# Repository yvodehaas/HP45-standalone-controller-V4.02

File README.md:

# HP45-standalone-controller-V4.02
HP45 standalone controller V4.02

This github repository is a direct upload of the HP45 Standalone controller V4.02.

This version uses a Teensy 3.5, has all the extra circuits to use DMA for inkjet, and has self testing capabilities. 
A more detailed set of information can be found here: https://ytec3d.com/hp45-controller-v4/

The firmware to run on this board is found here: https://github.com/yvodehaas/HP45-standalone-V4
And the software to control it is found here: https://github.com/yvodehaas/Inkjet-commander
Oasis controller also works on this controller, though it will only work in an Oasis based machine: https://hackaday.io/project/86954-oasis-3dp

This project has been discontinued on my side and is uploaded in the hope that someone else can use it as a template or as is. It is provided without warranty.

The board has a few known issues to keep in mind:
- The reset pulse circuit that resets the TLC59213 using the 74HC123 NEEDS to work. Without this the TLC59213 stays powered. Best case this destroys the HP45 nozzles on the HP45, works case it first destroys the TLC59213, then the Teensy 3.5
- The TLC59213 has a direct connection to the Teensy 3.5. The TLC59213 breaking usually applies the 12V supply to the Teensy 3.5 pins, destroying it.
- The Address testing circuit sometimes gives false negatives. The controller will still print, but while throwing errors.
- The resistor accross the 4017 and 4081 circuit (address circuit) is there to raise the voltage for the nozzle check circuit. The HP45 has pulldown resistors that lowered the voltage on the test circuit sufficiently to stop being able to test.
- Temperature is an indication. The formula was based on 2 printheads while it is known that the HP45 has no accurate temperature sensor. 80C at startup is possible.
- The controller needs 3 pulses to fire all nozzles in an address. This is done 5 primitives, 5 primitives and 4 primitives on each address. This seems to be an issue in the HP45, where too much heat builds up, leading to misfirings. Varying the voltage on the VHD should make this better, but this needs to be calibrated for each printhead.

This list will get appended when more issues are found.

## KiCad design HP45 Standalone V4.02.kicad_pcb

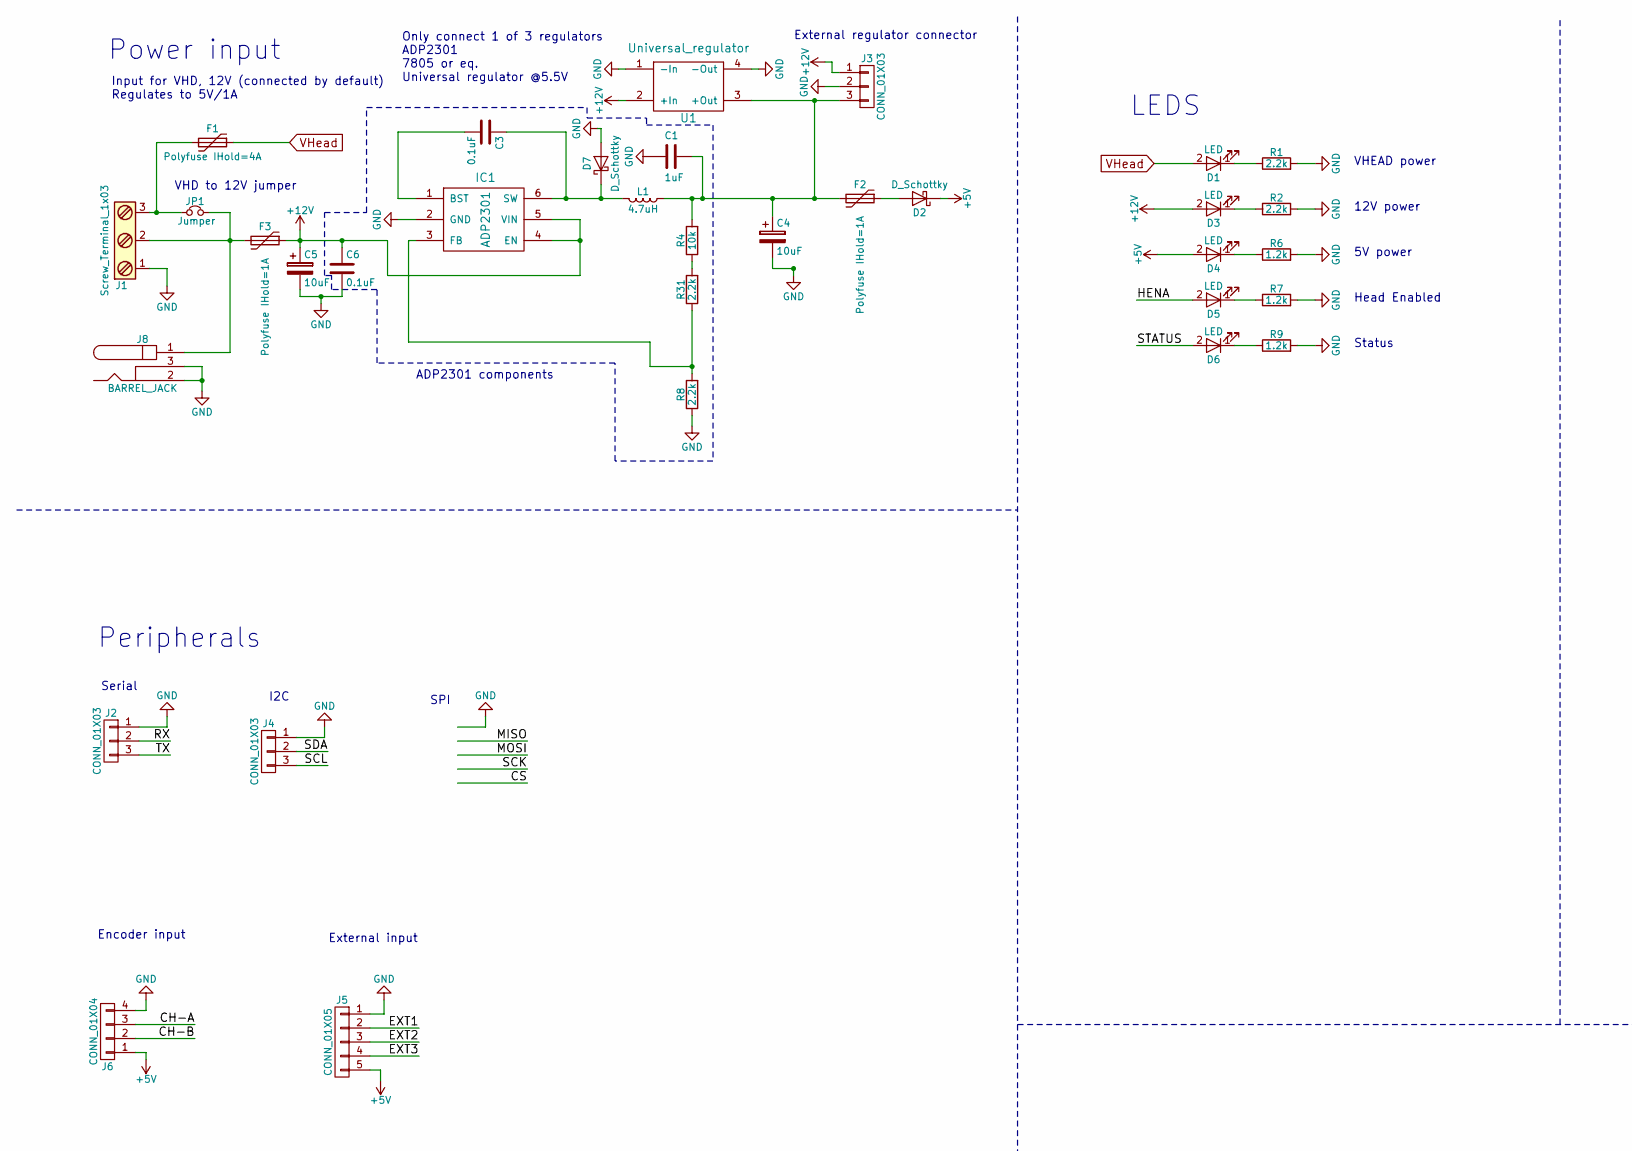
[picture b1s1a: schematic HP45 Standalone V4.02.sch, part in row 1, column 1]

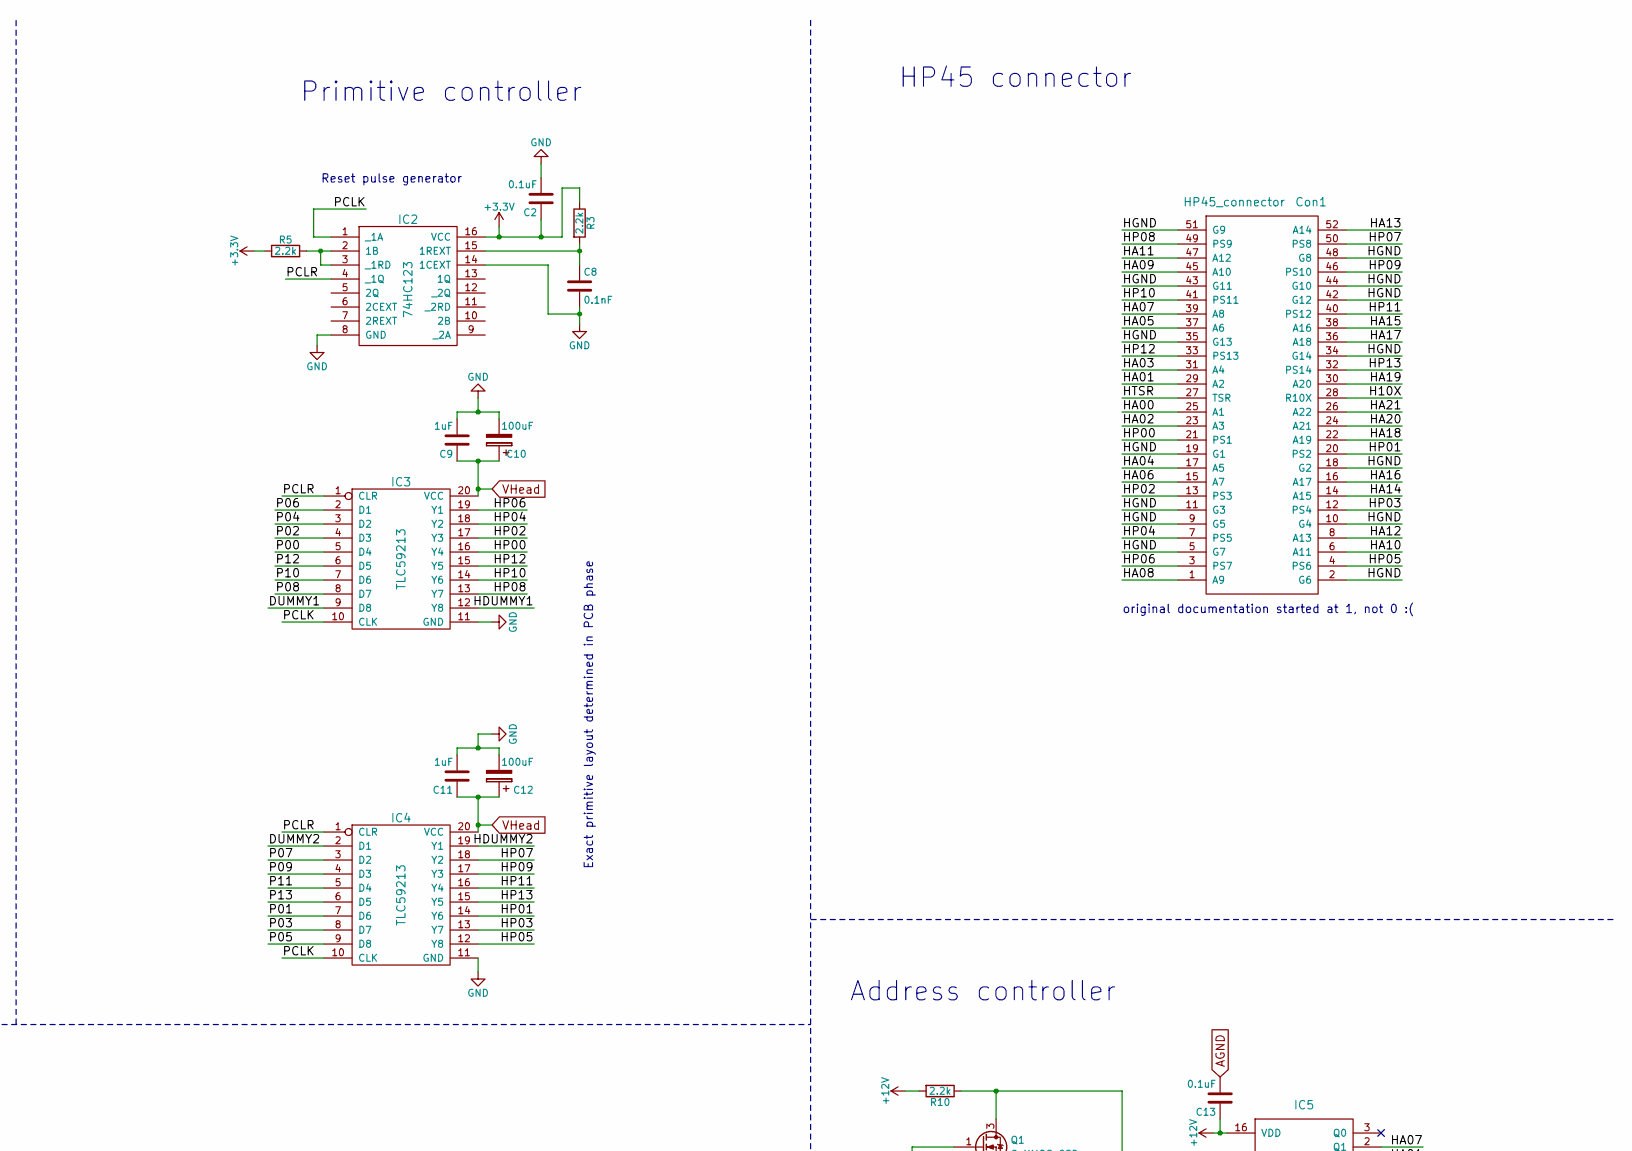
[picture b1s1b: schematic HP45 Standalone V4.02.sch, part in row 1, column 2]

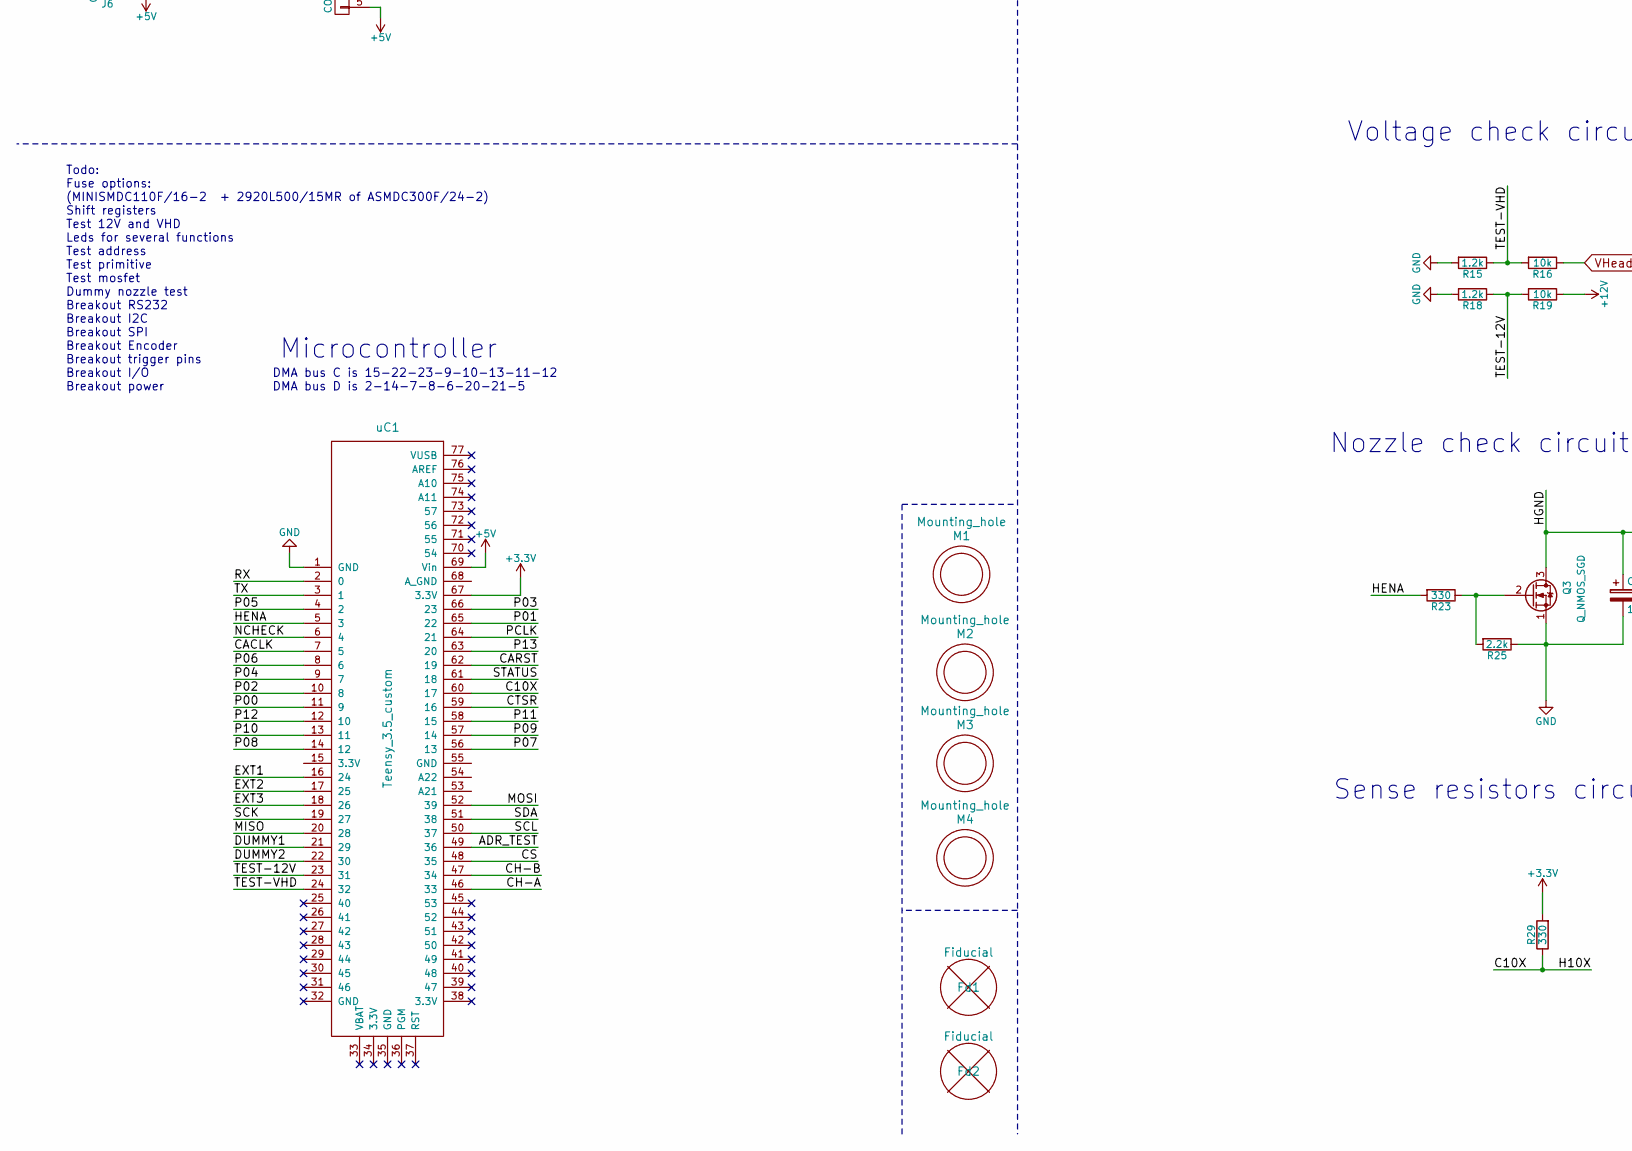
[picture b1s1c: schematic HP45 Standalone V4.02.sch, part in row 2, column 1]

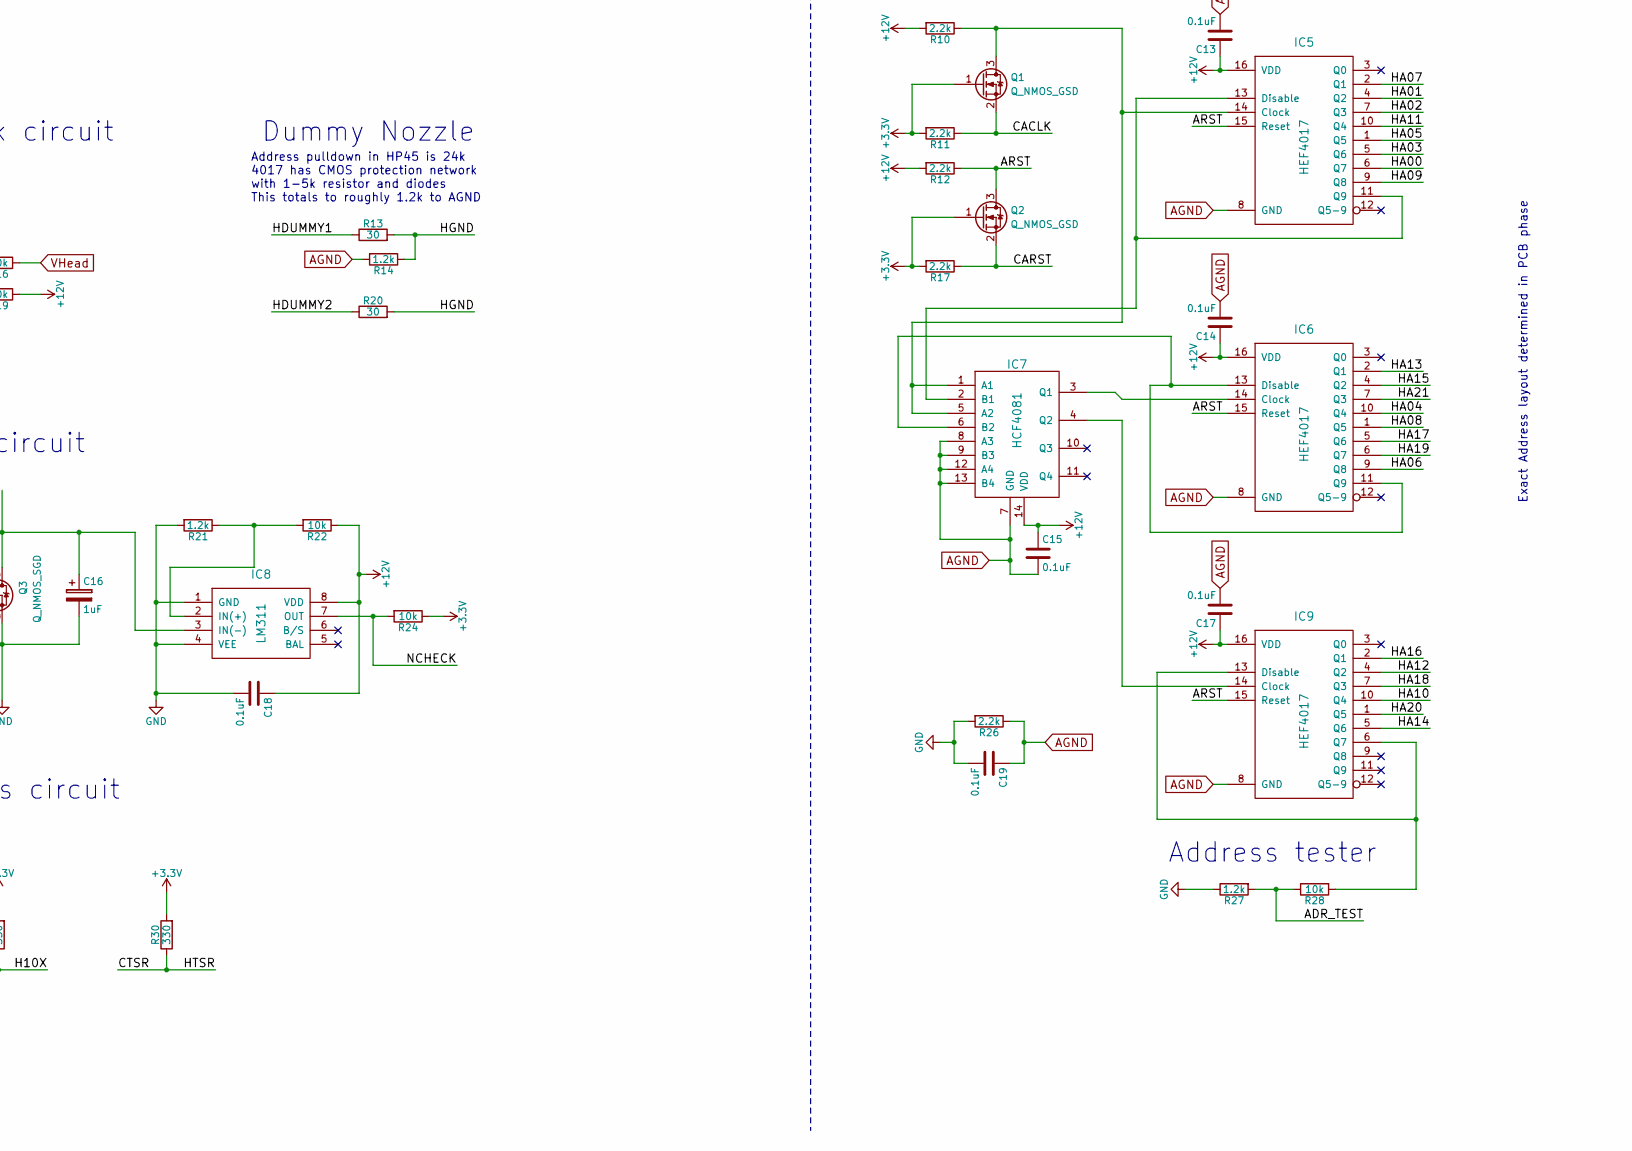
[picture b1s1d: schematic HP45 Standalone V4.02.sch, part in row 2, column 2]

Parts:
C1, C9, C11: 1uF; C_0603
C2, C3, C6, C13, C14, C15, C17, C18, C19: 0.1uF; C_0603
C4, C5: 10uF; CP_Elec_4x5.8
C8: 0.1nF; C_0603
C10, C12: 100uF; CP_Elec_8x10
C16: 1uF; CP_Elec_4x5.8
Con1: HP45_connector; HP45_SMD_connector
D1, D3, D4, D5, D6: LED; LED_0603
D2, D7: D_Schottky; D_SOD-323HE
F1: Polyfuse IHold=4A; Universal_PTC
F2, F3: Polyfuse IHold=1A; R_1812
Fd1, Fd2: Fiducial; Fiducial_1mm_Dia_2mm_Outer
IC1: ADP2301; TSOP-6_1.65x3.05mm_Pitch0.95mm
IC2: 74HC123; TSSOP-16_4.4x5mm_Pitch0.65mm
IC3, IC4: TLC59213; TSSOP-20_4.4x6.5mm_Pitch0.65mm
IC5, IC6, IC9: HEF4017; SSOP-16_4.4x5.2mm_Pitch0.65mm
IC7: HCF4081; TSSOP-14_4.4x5mm_Pitch0.65mm
IC8: LM311; SOIC-8_3.9x4.9mm_Pitch1.27mm
J1: Screw_Terminal_1x03; 3.5mm_screw_terminal
J2, J4: CONN_01X03; JST_XH_B03B-XH-A_03x2.50mm_Straight
J3: CONN_01X03; Pin_Header_Straight_1x03_Pitch2.54mm
J5: CONN_01X05; JST_XH_B05B-XH-A_05x2.50mm_Straight
J6: CONN_01X04; JST_XH_B04B-XH-A_04x2.50mm_Straight
J8: BARREL_JACK
JP1: Jumper; NC_Jumper
L1: 4.7uH; Inductor_Taiyo-Yuden_NR-50xx_HandSoldering
M1, M2, M3, M4: Mounting_hole; MountingHole_3.2mm_M3_Pad_Via
Q1, Q2: Q_NMOS_GSD; SOT-23
Q3: Q_NMOS_SGD; SO-8_PowerPAK
R1, R2, R3, R5, R8, R10, R11, R12, R17, R25, R26, R31: 2.2k; R_0603
R4, R16, R19, R22, R24, R28: 10k; R_0603
R6, R7, R9, R14, R15, R18, R21, R27: 1.2k; R_0603
R13, R20: 30; R_0805
R23, R29, R30: 330; R_0603
U1: Universal_regulator
uC1: Teensy_3.5_custom; Teensy_3.5_edges

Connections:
+3V3: C2.1, IC2.16 (VCC), Q1.1 (G), Q2.1 (G), R3.1, R5.1, R11.2, R17.2, R24.1, R29.2, R30.2, uC1.67 (3.3V)
+5V: D2.1 (K), D4.2 (A), J5.5, J6.1, uC1.69 (Vin)
+12V: C5.1, C6.1, C13.1, C14.1, C15.1, C17.1, C18.1, D3.2 (A), F3.1, IC1.4 (EN), IC1.5 (VIN), IC5.16 (VDD), IC6.16 (VDD), IC7.14 (VDD), IC8.8 (VDD), IC9.16 (VDD), J3.1, R10.2, R12.2, R19.1, R22.1, U1.2 (+In)
/ADR_TEST: R27.2, R28.1, uC1.49 (36)
/ARST: IC5.15 (Reset), IC6.15 (Reset), IC9.15 (Reset), Q2.3 (D), R12.1
/C10X: Con1.28 (R10X), R29.1, uC1.60 (17)
/CACLK: Q1.2 (S), R11.1, uC1.7 (5)
/CARST: Q2.2 (S), R17.1, uC1.62 (19)
/CH-A: J6.3, uC1.46 (33)
/CH-B: J6.2, uC1.47 (34)
/CTSR: Con1.27 (TSR), R30.1, uC1.59 (16)
/DUMMY1: IC3.9 (D8), uC1.21 (29)
/DUMMY2: IC4.2 (D1), uC1.22 (30)
/EXT1: J5.2, uC1.16 (24)
/EXT2: J5.3, uC1.17 (25)
/EXT3: J5.4, uC1.18 (26)
/HA00: Con1.25 (A1), IC5.6 (Q7)
/HA01: Con1.29 (A2), IC5.4 (Q2)
/HA02: Con1.23 (A3), IC5.7 (Q3)
/HA03: Con1.31 (A4), IC5.5 (Q6)
/HA04: Con1.17 (A5), IC6.10 (Q4)
/HA05: Con1.37 (A6), IC5.1 (Q5)
/HA06: Con1.15 (A7), IC6.9 (Q8)
/HA07: Con1.39 (A8), IC5.2 (Q1)
/HA08: Con1.1 (A9), IC6.1 (Q5)
/HA09: Con1.45 (A10), IC5.9 (Q8)
/HA10: Con1.6 (A11), IC9.10 (Q4)
/HA11: Con1.47 (A12), IC5.10 (Q4)
/HA12: Con1.8 (A13), IC9.4 (Q2)
/HA13: Con1.52 (A14), IC6.2 (Q1)
/HA14: Con1.14 (A15), IC9.5 (Q6)
/HA15: Con1.38 (A16), IC6.4 (Q2)
/HA16: Con1.16 (A17), IC9.2 (Q1)
/HA17: Con1.36 (A18), IC6.5 (Q6)
/HA18: Con1.22 (A19), IC9.7 (Q3)
/HA19: Con1.30 (A20), IC6.6 (Q7)
/HA20: Con1.24 (A21), IC9.1 (Q5)
/HA21: Con1.26 (A22), IC6.7 (Q3)
/HDUMMY1: IC3.12 (Y8), R13.1
/HDUMMY2: IC4.19 (Y1), R20.1
/HENA: D5.2 (A), R23.2, uC1.5 (3)
/HGND: C16.1, Con1.2 (G6), Con1.5 (G7), Con1.9 (G5), Con1.10 (G4), Con1.11 (G3), Con1.18 (G2), Con1.19 (G1), Con1.34 (G14), Con1.35 (G13), Con1.42 (G12), Con1.43 (G11), Con1.44 (G10), Con1.48 (G8), Con1.51 (G9), IC8.3 (IN(-)), Q3.3 (D), R13.2, R14.1, R20.2
/HP00: Con1.21 (PS1), IC3.16 (Y4)
/HP01: Con1.20 (PS2), IC4.14 (Y6)
/HP02: Con1.13 (PS3), IC3.17 (Y3)
/HP03: Con1.12 (PS4), IC4.13 (Y7)
/HP04: Con1.7 (PS5), IC3.18 (Y2)
/HP05: Con1.4 (PS6), IC4.12 (Y8)
/HP06: Con1.3 (PS7), IC3.19 (Y1)
/HP07: Con1.50 (PS8), IC4.18 (Y2)
/HP08: Con1.49 (PS9), IC3.13 (Y7)
/HP09: Con1.46 (PS10), IC4.17 (Y3)
/HP10: Con1.41 (PS11), IC3.14 (Y6)
/HP11: Con1.40 (PS12), IC4.16 (Y4)
/HP12: Con1.33 (PS13), IC3.15 (Y5)
/HP13: Con1.32 (PS14), IC4.15 (Y5)
/NCHECK: IC8.7 (OUT), R24.2, uC1.6 (4)
/P00: IC3.5 (D4), uC1.11 (9)
/P01: IC4.7 (D6), uC1.65 (22)
/P02: IC3.4 (D3), uC1.10 (8)
/P03: IC4.8 (D7), uC1.66 (23)
/P04: IC3.3 (D2), uC1.9 (7)
/P05: IC4.9 (D8), uC1.4 (2)
/P06: IC3.2 (D1), uC1.8 (6)
/P07: IC4.3 (D2), uC1.56 (13)
/P08: IC3.8 (D7), uC1.14 (12)
/P09: IC4.4 (D3), uC1.57 (14)
/P10: IC3.7 (D6), uC1.13 (11)
/P11: IC4.5 (D4), uC1.58 (15)
/P12: IC3.6 (D5), uC1.12 (10)
/P13: IC4.6 (D5), uC1.63 (20)
/PCLK: IC2.1 (_1A), IC3.10 (CLK), IC4.10 (CLK), uC1.64 (21)
/PCLR: IC2.4 (_1Q), IC3.1 (CLR), IC4.1 (CLR)
/RX: J2.2, uC1.2 (0)
/SCL: J4.3, uC1.50 (37)
/SDA: J4.2, uC1.51 (38)
/STATUS: D6.2 (A), uC1.61 (18)
/TEST-12V: R18.1, R19.2, uC1.23 (31)
/TEST-VHD: R15.1, R16.2, uC1.24 (32)
/TX: J2.3, uC1.3 (1)
AGND: C13.2, C14.2, C15.2, C17.2, C19.1, IC5.8 (GND), IC6.8 (GND), IC7.7 (GND), IC7.8 (A3), IC7.9 (B3), IC7.12 (A4), IC7.13 (B4), IC9.8 (GND), R14.2, R26.1
GND: C1.2, C2.2, C4.2, C5.2, C6.2, C8.2, C9.2, C10.2, C11.2, C12.2, C16.2, C18.2, C19.2, D7.2 (A), IC1.2 (GND), IC2.8 (GND), IC2.14 (1CEXT), IC3.11 (GND), IC4.11 (GND), IC8.1 (GND), IC8.4 (VEE), J1.1, J2.1, J3.2, J4.1, J5.1, J6.4, J8.2, J8.3, Q3.1 (S), R1.2, R2.2, R6.2, R7.2, R8.1, R9.2, R15.2, R18.2, R21.2, R25.1, R26.2, R27.1, U1.1 (-In), U1.4 (-Out), uC1.1 (GND)
unnamed: C1.1, C4.1, F2.2, J3.3, L1.1, R4.2, U1.3 (+Out)
unnamed: C3.1, D7.1 (K), IC1.6 (SW), L1.2
unnamed: C3.2, IC1.1 (BST)
unnamed: C8.1, IC2.15 (1REXT), R3.2
unnamed: D1.1 (K), R1.1
unnamed: D2.2 (A), F2.1
unnamed: D3.1 (K), R2.1
unnamed: D4.1 (K), R6.1
unnamed: D5.1 (K), R7.1
unnamed: D6.1 (K), R9.1
unnamed: F1.2, J1.3, JP1.1
unnamed: F3.2, J1.2, J8.1, JP1.2
unnamed: IC1.3 (FB), R8.2, R31.1
unnamed: IC2.2 (1B), IC2.3 (_1RD), R5.2
unnamed: IC5.11 (Q9), IC5.13 (Disable), IC7.2 (B1)
unnamed: IC5.14 (Clock), IC7.1 (A1), IC7.5 (A2), Q1.3 (D), R10.1
unnamed: IC6.11 (Q9), IC6.13 (Disable), IC7.6 (B2)
unnamed: IC6.14 (Clock), IC7.3 (Q1)
unnamed: IC7.4 (Q2), IC9.14 (Clock)
unnamed: IC8.2 (IN(+)), R21.1, R22.2
unnamed: IC9.6 (Q7), IC9.13 (Disable), R28.2
unnamed: Q3.2 (G), R23.1, R25.2
unnamed: R4.1, R31.2
VHead: C9.1, C10.1, C11.1, C12.1, D1.2 (A), F1.1, IC3.20 (VCC), IC4.20 (VCC), R16.1

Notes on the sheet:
Address controller
Primitive controller
HP45 connector
Nozzle check circuit
Exact primitive layout determined in PCB phase
Exact Address layout determined in PCB phase
Sense resistors circuit
original documentation started at 1, not 0 :(
VHD to 12V jumper
Power input
Input for VHD, 12V (connected by default) Regulates to 5V/1A
Todo: Fuse options: (MINISMDC110F/16-2 + 2920L500/15MR of ASMDC300F/24-2) Shift registers Test 12V and VHD Leds for several functions Test address Test primitive Test mosfet Dummy nozzle test Breakout RS232 Breakout I2C Breakout SPI Breakout Encoder Breakout trigger pins Breakout I/O Breakout power
LEDS
12V power
5V power
Head Enabled
Status
Serial
Encoder input
Voltage check circuit
Microcontroller
Peripherals
Dummy Nozzle
Address tester
DMA bus C is 15-22-23-9-10-13-11-12 DMA bus D is 2-14-7-8-6-20-21-5
Address pulldown in HP45 is 24k 4017 has CMOS protection network with 1-5k resistor and diodes This totals to roughly 1.2k to AGND
VHEAD power
External input
Reset pulse generator
I2C
SPI
External regulator connector
Only connect 1 of 3 regulators ADP2301 7805 or eq. Universal regulator @5.5V
ADP2301 components

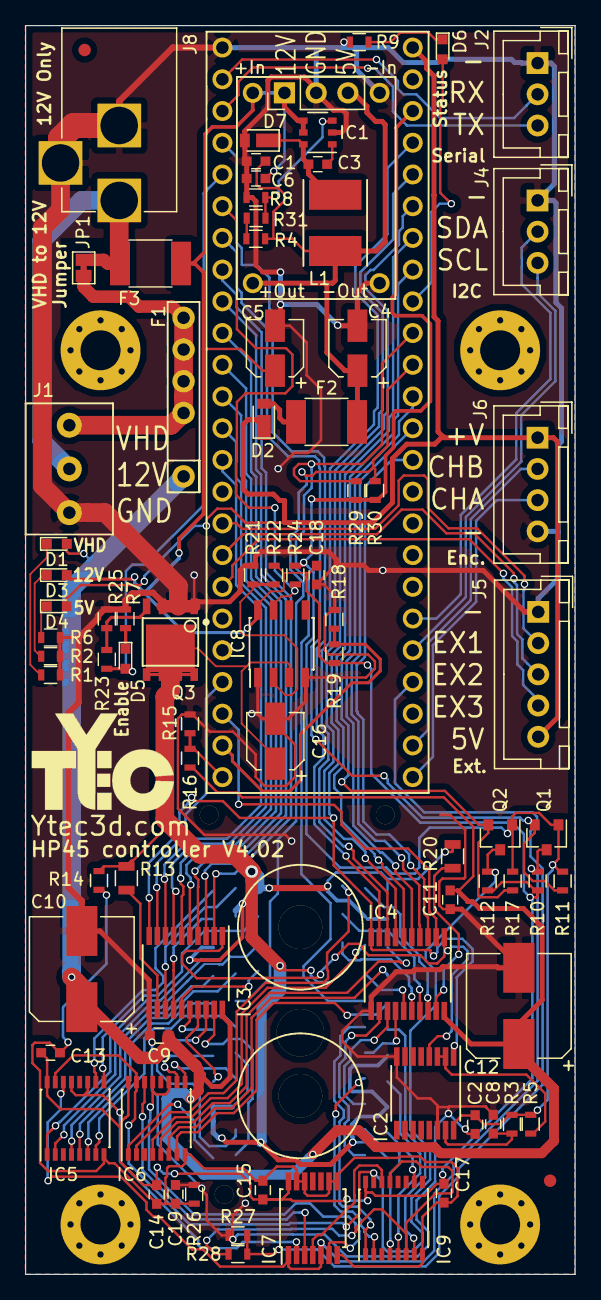
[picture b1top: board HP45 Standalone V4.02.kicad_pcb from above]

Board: 2 copper layers, 44.0 x 100.0 mm, 89 parts (1 on the bottom side), 106 nets.

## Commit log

2024-11-27 Add files via upload
    Added cache file required to repair the schematic
